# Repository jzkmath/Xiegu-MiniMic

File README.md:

# Xiegu-MiniMic
A Small Microphone for the Xiegu G90, X5105 and X6100 Radios. I have designed this to be assembled mostly by JLCPCB. (See below for instructions on how to order them)

After looking at the larger Microphone that comes with the radio, it appears to be a clone of the ICOM HM151 Hand Mic. Knowing this, I was able to use the service manual to create this PCB.

This is designed using KiCad Version 6.0.9

The Enclosure can be 3D Printed and requires 4 M2x20mm Socket Head Screws and 4 M2 Nuts. I used McMaster Carr Part numbers 91292A013 and 90591A111 for this project.

## Version History:

Rev. A: Initial Design

Rev. B: Found that the EM6022P Microphone Element was wired backwards. Fixed it in this revision.

## PCB Assembly Instructions:

1. Download this repository by clicking on "code" then downloading as a ZIP file. Extract the ZIP file.
2. Go to https://jlcpcb.com/quote
3. Click "Add Gerber File" upload the `Xiegu-MiniMic-GERBER.zip` file found in the `GERBER` folder.
4. Adjust settings. The only ones you should change (if you want) is PCB Qty, PCB Color, and Surface Finish. 
  - If you just want the PCB you may click "Save to Cart" and place your order.
  - If you want assembly, proceed to step 5.
5. Scroll don and tick the slider to the right of "PCB Assembly"
6. Leave it set to "Assemble Top Side" and click "Confirm"
7. For the "BOM File" upload `Xiegu MiniMic.csv` in the `ASSEMBLY` folder.
8. For the "CPL File" upload `Xiegu MiniMic-top-pos.csv` in the `ASSEMBLY` folder.
9. For Usage, I recommend you set it to "Research/Education/DIY/Entertainment > DIY HS Code 902300" (You can really set it to whatever you want)
10. Click "Next"
11. Make sure the BOM is complete (except for the RJ45 connector) 
  - If one of the parts are out of stock, you can substitute with a similar part. 
  - For resistors and capacitors, the main thing to ensure is the value and the case is 0805 (except for C3)
  - C3 is an electrolytic capacitor. Specs needed: 10uF, at least 16V, Diameter: 4mm, Length: 5.4mm (SMD)
  - Zener Diodes are 9.1v, and have a SOD-123 package
  - Inductor L1 is 33uH and has a 1008 package size
12. Once any substitutions are made, click "Next"
13. Inspect the render to make sure the orientation is correct. C3 should have the plus line up and the diodes should have their negative on the right side, matching up with the silkscreen.
14. Click "Add to Cart" then place your order.

You will likely need to order the RJ45 connector (54602-908LF) and microphone (EM6022P) from Digikey or Mouser and solder them yourself.

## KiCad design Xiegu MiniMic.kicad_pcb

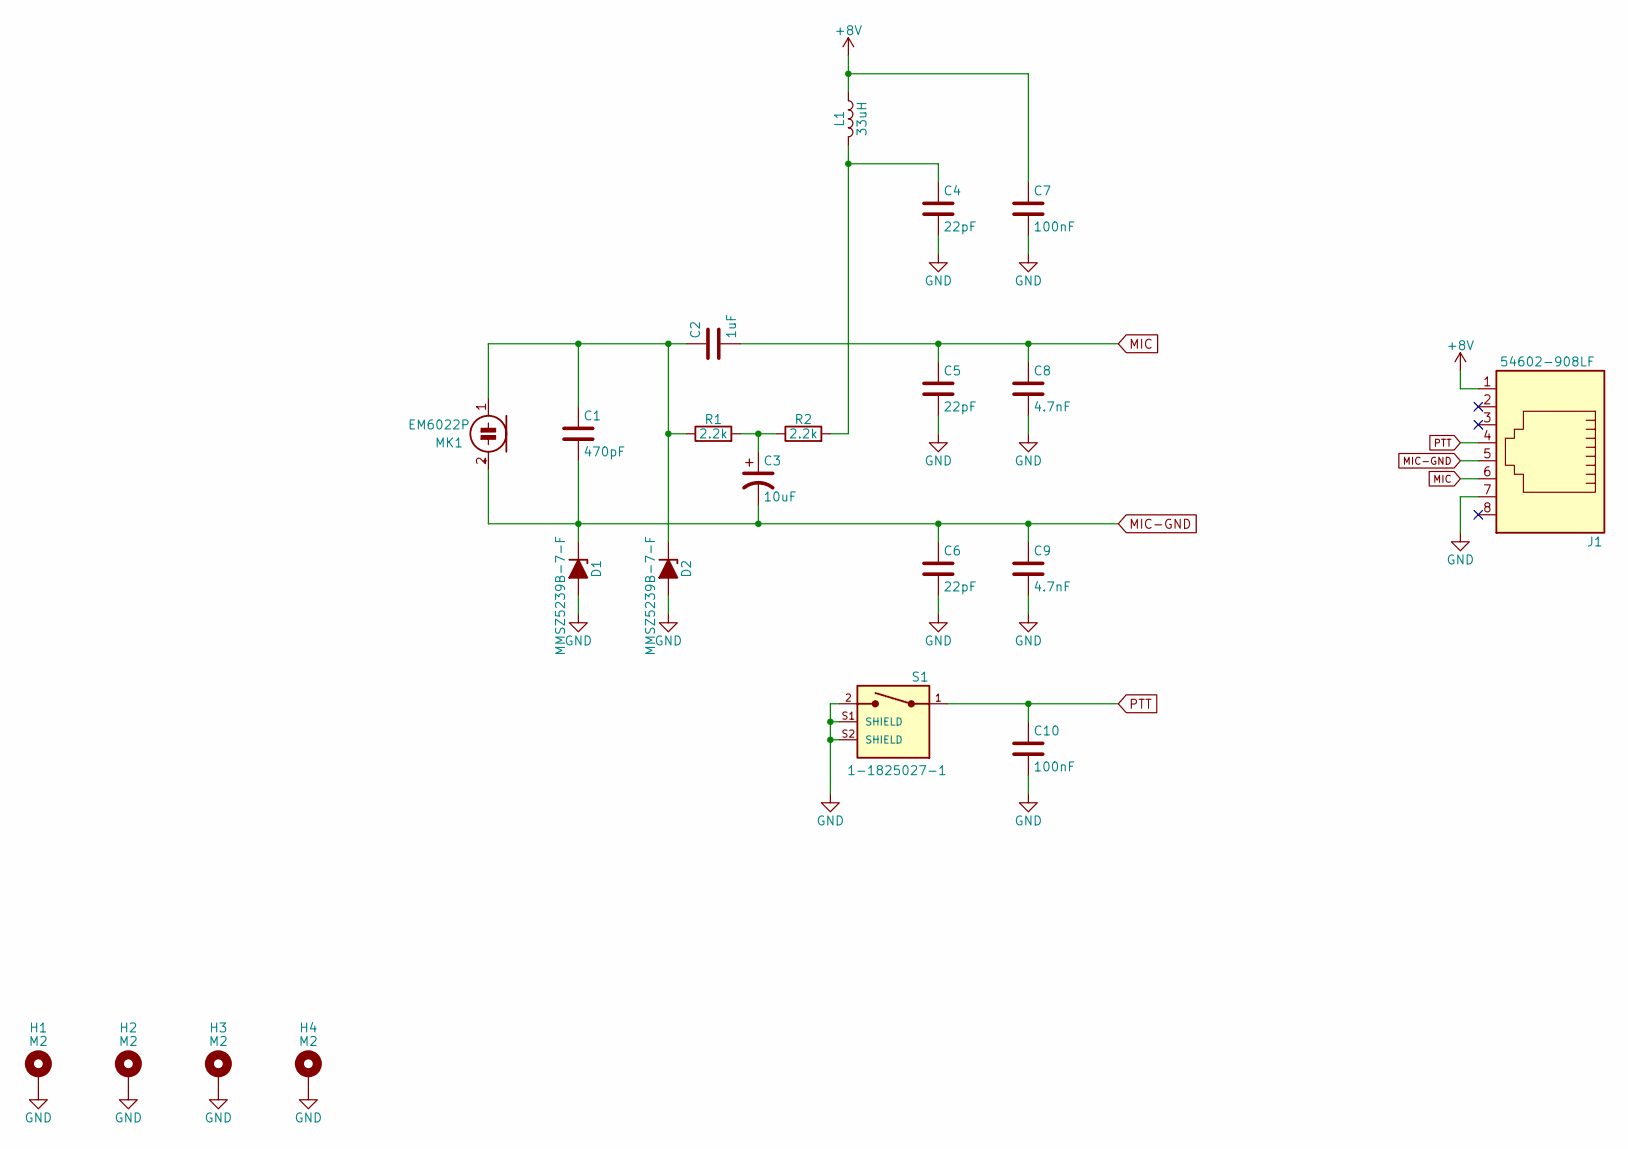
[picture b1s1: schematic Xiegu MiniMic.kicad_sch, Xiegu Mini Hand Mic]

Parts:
C1: 470pF; C_0805_2012Metric; MPN 08055A471JAT2A; Digikey PN 478-1324-1-ND
C2: 1uF; C_0805_2012Metric; MPN 0805YC105KAT2A; Digikey PN 478-5034-1-ND
C3: 10uF; CP_Elec_4x5.4; MPN UWT1C100MCL1GB; Digikey PN 493-2173-1-ND
C4, C5, C6: 22pF; C_0805_2012Metric; MPN 08055A220JAT2A; Digikey PN 478-1308-1-ND
C7, C10: 100nF; C_0805_2012Metric; MPN 08055C104KAT4A; Digikey PN 478-10836-1-ND
C8, C9: 4.7nF; C_0805_2012Metric; MPN 08055C472K4T4A; Digikey PN 478-08055C472K4T4ACT-ND
D1, D2: MMSZ5239B-7-F; D_SOD-123; MPN MMSZ5239B-7-F; Digikey PN MMSZ5239B-FDICT-ND
H1, H2, H3, H4: M2; MountingHole_2.2mm_M2_Pad
J1: 54602-908LF; RJ45_Amphenol_54602-x08_Horizontal; MPN 54602-908LF; Digikey PN 609-1046-ND
L1: 33uH; L_1008_2520Metric; MPN NLV25T-330J-EF; Digikey PN 445-16476-1-ND
MK1: EM6022P; MPN EM-6022P; Digikey PN 433-1088-ND
R1, R2: 2.2k; R_0805_2012Metric; MPN CRG0805F2K2; Digikey PN A106060CT-ND
S1: 1-1825027-1; SW_1-1825027-1; MPN 1-1825027-1; Digikey PN 450-1658-ND

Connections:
+8V: C7.1, J1.1, L1.1
GND: C4.2, C5.2, C6.2, C7.2, C8.2, C9.2, C10.2, D1.2 (A), D2.2 (A), H1.1, H2.1, H3.1, H4.1, J1.7, S1.2, S1.S1 (SHIELD), S1.S2 (SHIELD)
MIC: C2.2, C5.1, C8.1, J1.6
MIC-GND: C1.2, C3.2, C6.1, C9.1, D1.1 (K), J1.5, MK1.2 (+)
unnamed: C1.1, C2.1, D2.1 (K), MK1.1 (-), R1.1
unnamed: C3.1, R1.2, R2.1
unnamed: C4.1, L1.2, R2.2
PTT: C10.1, J1.4, S1.1

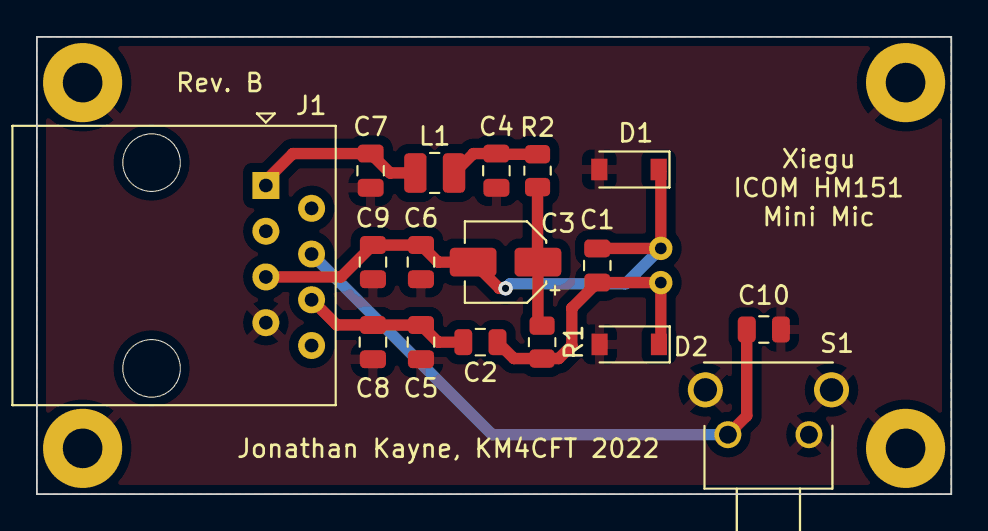
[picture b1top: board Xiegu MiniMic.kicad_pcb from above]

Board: 2 copper layers, 50.8 x 25.4 mm, 22 parts (1 on the bottom side), 8 nets.

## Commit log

2022-11-16 Rev B
2022-11-16 Create LICENSE
2022-11-17 Fixed hardware tolerance
2022-11-18 added PCB assembly instructions
